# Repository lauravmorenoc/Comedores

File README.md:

# Comedores
Uno de los servicios que se busca mejorar por medio del proyecto "Campus Inteligente", corresponde al servicio de comedores de la Universidad Nacional de Colombia, sede Bogotá.

## Funcionamiento actual del sistema en la Universidad
Actualmente, los usuarios se dirigen a cualquiera de los comedores de la universidad, sin conocimiento previo de qué tan lleno se encuentra. Al llegar, hacen una fila física hasta el lugar en el que se sirven los almuerzos. Una vez aquí, toman una bandeja, y los empleados van presentando las opciones disponibles (por ejemplo, para escoger entre carne de res o pollo), de las cuales los usuarios eligen su opción favorita. En base a esta información, los empleados llenan los platos, que se van colocando en la bandeja. Al finalizar, se dirigen a la caja, en donde un operador les cobra una tarifa que depende si es estudiante sin beneficio alimentario, estudiante con este beneficio u otro tipo de usuario (visitante, docente, entre otros).

La siguiente imagen resume los aspectos anteriormente mencionados

## Primera solución presentada

## regulaciones respecto al uso del espectro electromagnético.

### Espectro electromagnético
Es la distribución energética del conjunto de las ondas electromagnéticas, yendo desde la longitud de onda más grande, a la longitud de onda más pequeña (o desde la frecuencia más baja, a la frecuencia más alta).

Uno de los usos principales del espectro son las telecomunicaciones, y por esta razón está regulado por el gobierno la radiación, distribución y recepción de las diferentes frecuencias. Las bandas varían dependiendo de la frecuencia/longitud de onda en varios grupos estándar:

Comparando los diferentes estándares se ven de la siguiente forma:

Respecto al espectro hay algunas regulaciones que es pertinente mencionar en relación al proyecto.

### Regulaciones
_Basado en el decreto 1078 de 2015 y la resolución 711 de 2016 de la ANE (Agencia Nacional del Espectro)_

#### Frecuencias para aplicaciones industriales, científicas y médicas (ICM)
Funcionamiento de equipos o de instalaciones destinados a producir y utilizar, en un espacio reducido, energía radioeléctrica con fines industriales, científicos y médicos, domésticos o similares, con exclusión de todas las aplicaciones de telecomunicación. Se muestran en la siguiente tabla:

Estas frecuencias pueden ser usadas para radiocomunicaciones de corto alcance (RCA), pero el usuario deben aceptar la potencial interferencia que se puede producir.

#### Frecuencias restringidas

Con el fin de evitar posibles interferencias a comunicaciones radioeléctricas sensibles tales como radionavegación aeronáutica, radioastronomía, operaciones de búsqueda y rescate y comunicaciones móviles, entre otras, los dispositivos de radiocomunicaciones de corto alcance y baja potencia (RCA) no podrán funcionar en las bandas descritas en la siguiente tabla:

#### Radiador intencional/radio aficionado
_Radiador intencional: Persona con interés en hacer algún tipo de transmisión usando el espectro._
_Radioaficionado: Persona con interés no comercial de hacer algún tipo de transmisión usando el espectro_

Para usar el espectro de forma comercial, la persona/entidad debe registrarse en el registro único del MINTIC, y ya que el uso será comercial, deben pagar contraprestaciones (impuestos) por el uso del espectro.

Los radioaficionados pueden usar el espectro sin pagar contraprestaciones. existen tres tipos de licencias para radioaficionados:

- Segunda o de Novicio
- Primera o de Experto
- Avanzada

#### Límites para radiadores intencionales o radio aficionados

A menos de estar incluido en alguna de las excepciones, las emisiones de cualquier radiador intencional no deberán superar los niveles de intensidad de campo que se especifican en la siguiente tabla:

A su vez estas son las restricciones de bandas y tipo de emisión:

#### Antenas

No se permite la operación de dispositivos con antenas diferentes a las suministradas o recomendadas por el fabricante, así mismo, no se pueden usar antenas que permitan que el sistema exceda los límites de potencia o campo eléctrico establecidos por regulación.

#### Referencias

https://www.suin-juriscol.gov.co/viewDocument.asp?id=30019521
https://normograma.mintic.gov.co/mintic/docs/pdf/resolucion_ane_0711_2016.pdf

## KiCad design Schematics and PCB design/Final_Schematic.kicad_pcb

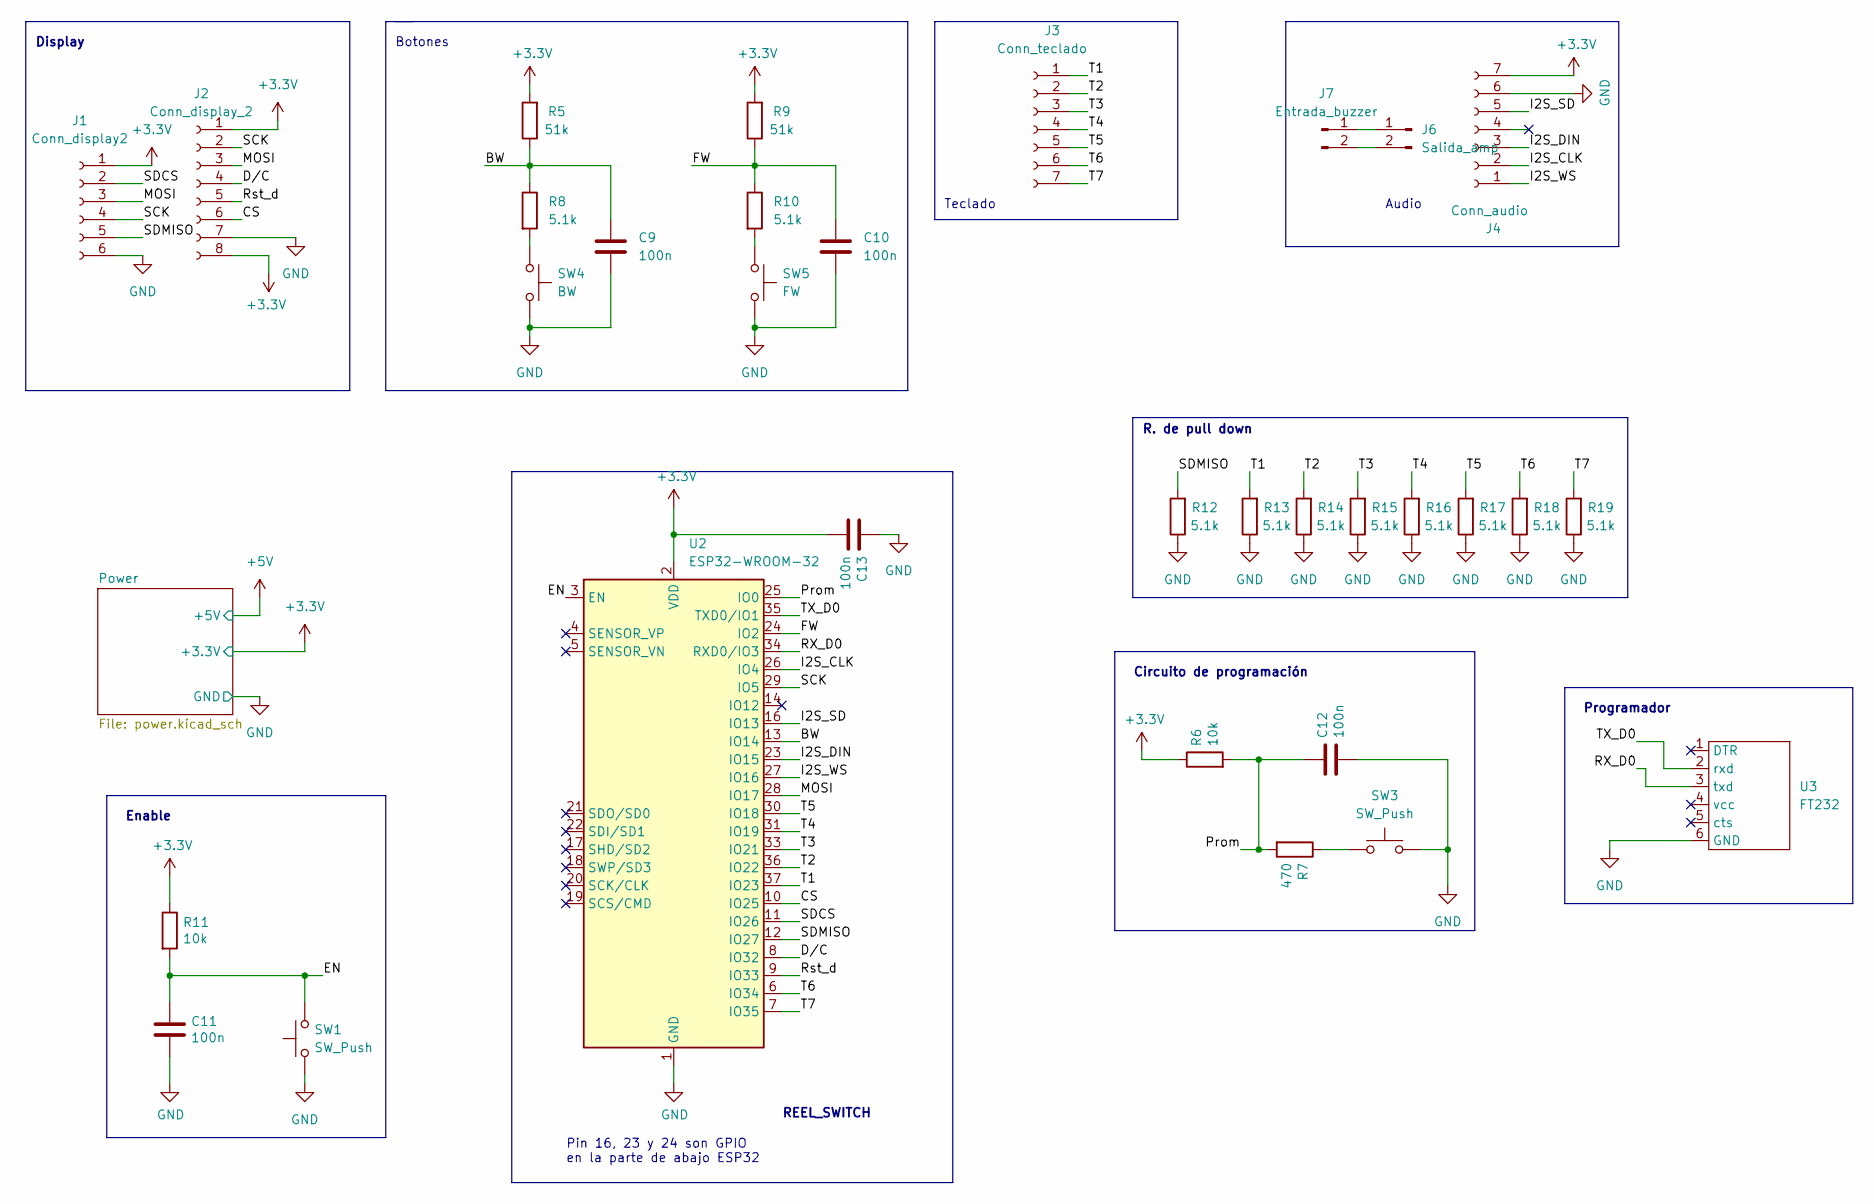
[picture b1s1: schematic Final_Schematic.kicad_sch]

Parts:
C9, C10, C11, C12, C13: 100n; C_0805_2012Metric_Pad1.18x1.45mm_HandSolder
J1: Conn_display2; PinHeader_1x06_P2.54mm_Vertical
J2: Conn_display_2; JST_EH_B8B-EH-A_1x08_P2.50mm_Vertical
J3: Conn_teclado; JST_EH_B7B-EH-A_1x07_P2.50mm_Vertical
J4: Conn_audio; PinSocket_1x07_P2.54mm_Vertical
J6: Salida_amp; PinSocket_1x02_P2.54mm_Vertical
J7: Entrada_buzzer; JST_EH_B2B-EH-A_1x02_P2.50mm_Vertical
R5, R9: 51k; R_0805_2012Metric_Pad1.20x1.40mm_HandSolder
R6, R11: 10k; R_0805_2012Metric_Pad1.20x1.40mm_HandSolder
R7: 470; R_0805_2012Metric_Pad1.20x1.40mm_HandSolder
R8, R10, R12, R13, R14, R15, R16, R17, R18, R19: 5.1k; R_0805_2012Metric_Pad1.20x1.40mm_HandSolder
SW1: SW_Push; SW_SPST_CK_RS282G05A3
SW3: SW_Push; SW_SPST_EVQQ2
SW4: BW; TerminalBlock_Altech_AK300-2_P5.00mm
SW5: FW; TerminalBlock_Altech_AK300-2_P5.00mm
U2: ESP32-WROOM-32
U3: FT232; PinSocket_1x06_P2.54mm_Vertical

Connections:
+3V3: C13.2, J1.1, J2.1, J2.8, J4.7, R5.2, R6.1, R9.2, R11.1, U2.2 (VDD); also elsewhere on the board
/BW: C9.2, R5.1, R8.1, U2.13 (IO14)
/CS: J2.6, U2.10 (IO25)
/D/C: J2.4, U2.8 (IO32)
/EN: C11.1, R11.2, SW1.2, U2.3 (EN)
/FW: C10.2, R9.1, R10.1, U2.24 (IO2)
/I2S_CLK: J4.2, U2.26 (IO4)
/I2S_DIN: J4.3, U2.23 (IO15)
/I2S_SD: J4.5, U2.16 (IO13)
/I2S_WS: J4.1, U2.27 (IO16)
/MOSI: J1.3, J2.3, U2.28 (IO17)
/Prom: C12.1, R6.2, R7.2, U2.25 (IO0)
/RX_D0: U2.34 (RXD0/IO3), U3.3 (txd)
/Rst_d: J2.5, U2.9 (IO33)
/SCK: J1.4, J2.2, U2.29 (IO5)
/SDCS: J1.2, U2.11 (IO26)
/SDMISO: J1.5, R12.2, U2.12 (IO27)
/T1: J3.1, R13.2, U2.37 (IO23)
/T2: J3.2, R14.2, U2.36 (IO22)
/T3: J3.3, R15.2, U2.33 (IO21)
/T4: J3.4, R16.2, U2.31 (IO19)
/T5: J3.5, R17.2, U2.30 (IO18)
/T6: J3.6, R18.2, U2.6 (IO34)
/T7: J3.7, R19.2, U2.7 (IO35)
/TX_D0: U2.35 (TXD0/IO1), U3.2 (rxd)
GND: C9.1, C10.1, C11.2, C12.2, C13.1, J1.6, J2.7, J4.6, R12.1, R13.1, R14.1, R15.1, R16.1, R17.1, R18.1, R19.1, SW1.1, SW3.2, SW4.2, SW5.2, U2.1 (GND), U2.15 (GND), U2.38 (GND), U2.39 (GND), U3.6 (GND); also elsewhere on the board
unnamed: J6.1, J7.1
unnamed: J6.2, J7.2
unnamed: R7.1, SW3.1
unnamed: R8.2, SW4.1
unnamed: R10.2, SW5.1

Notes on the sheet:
Circuito de programación
Botones
Pin 16, 23 y 24 son GPIO en la parte de abajo ESP32
R. de pull down
Display
Audio
Programador
Teclado
REEL_SWITCH
Enable

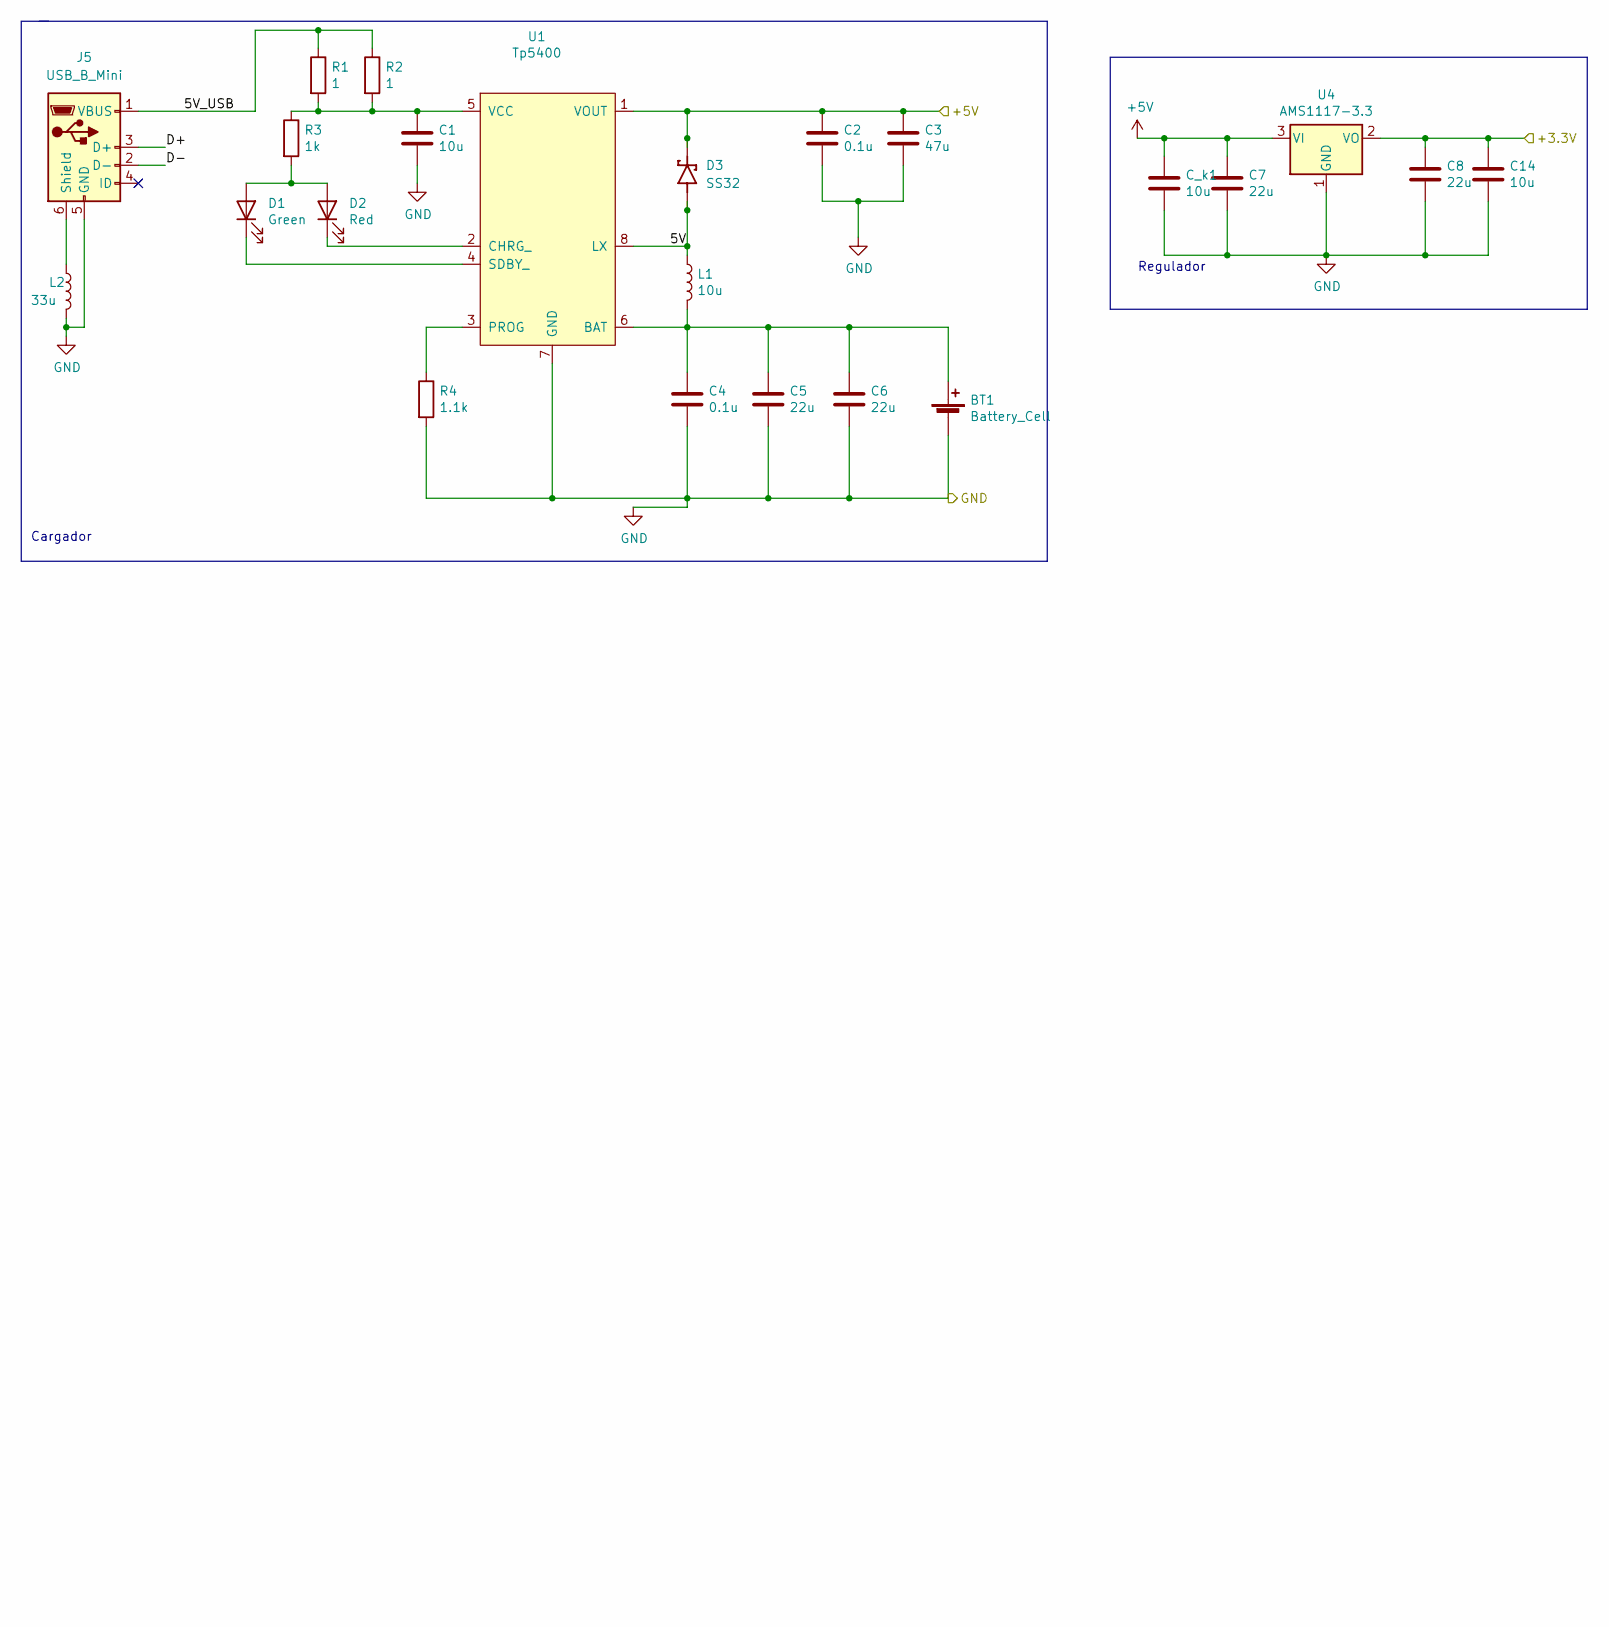
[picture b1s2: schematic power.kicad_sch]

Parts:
BT1: Battery_Cell; JST_PH_B2B-PH-K_1x02_P2.00mm_Vertical
C1, C14: 10u
C2, C4: 0.1u
C3: 47u
C5, C6, C7, C8: 22u
C_k1: 10u
D1: Green; LED_0805_2012Metric_Pad1.15x1.40mm_HandSolder
D2: Red; LED_0805_2012Metric_Pad1.15x1.40mm_HandSolder
D3: SS32; PARTREV Q2102
J5: USB_B_Mini; USB_Mini-B_AdamTech_MUSB-B5-S-VT-TSMT-1_SMD_Vertical
L1: 10u; L_6.3x6.3_H3
L2: 33u; L_6.3x6.3_H3
R1, R2: 1
R3: 1k
R4: 1.1k
U1: Tp5400; TP5410
U4: AMS1117-3.3; SOT-223-3_TabPin2

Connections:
+3V3: C8.1, C14.1, U4.2 (VO); also elsewhere on the board
+5V: C2.1, C3.1, C7.1, C_k1.1, D3.C, U1.1 (VOUT), U4.3 (VI)
/Power/5V: D3.A, L1.1, U1.8 (LX)
/Power/5V_USB: J5.1 (VBUS), R1.1, R2.1
/Power/D+: J5.3 (D+)
/Power/D-: J5.2 (D-)
GND: BT1.2 (-), C1.2, C2.2, C3.2, C4.2, C5.2, C6.2, C7.2, C8.2, C14.2, C_k1.2, J5.5 (GND), L2.2, R4.2, U1.7 (GND), U4.1 (GND); also elsewhere on the board
unnamed: BT1.1 (+), C4.1, C5.1, C6.1, L1.2, U1.6 (BAT)
unnamed: C1.1, R1.2, R2.2, R3.1, U1.5 (VCC)
unnamed: D1.1 (K), U1.4 (SDBY_)
unnamed: D1.2 (A), D2.2 (A), R3.2
unnamed: D2.1 (K), U1.2 (CHRG_)
unnamed: J5.6 (Shield), L2.1
unnamed: R4.1, U1.3 (PROG)

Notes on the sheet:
Regulador
Cargador

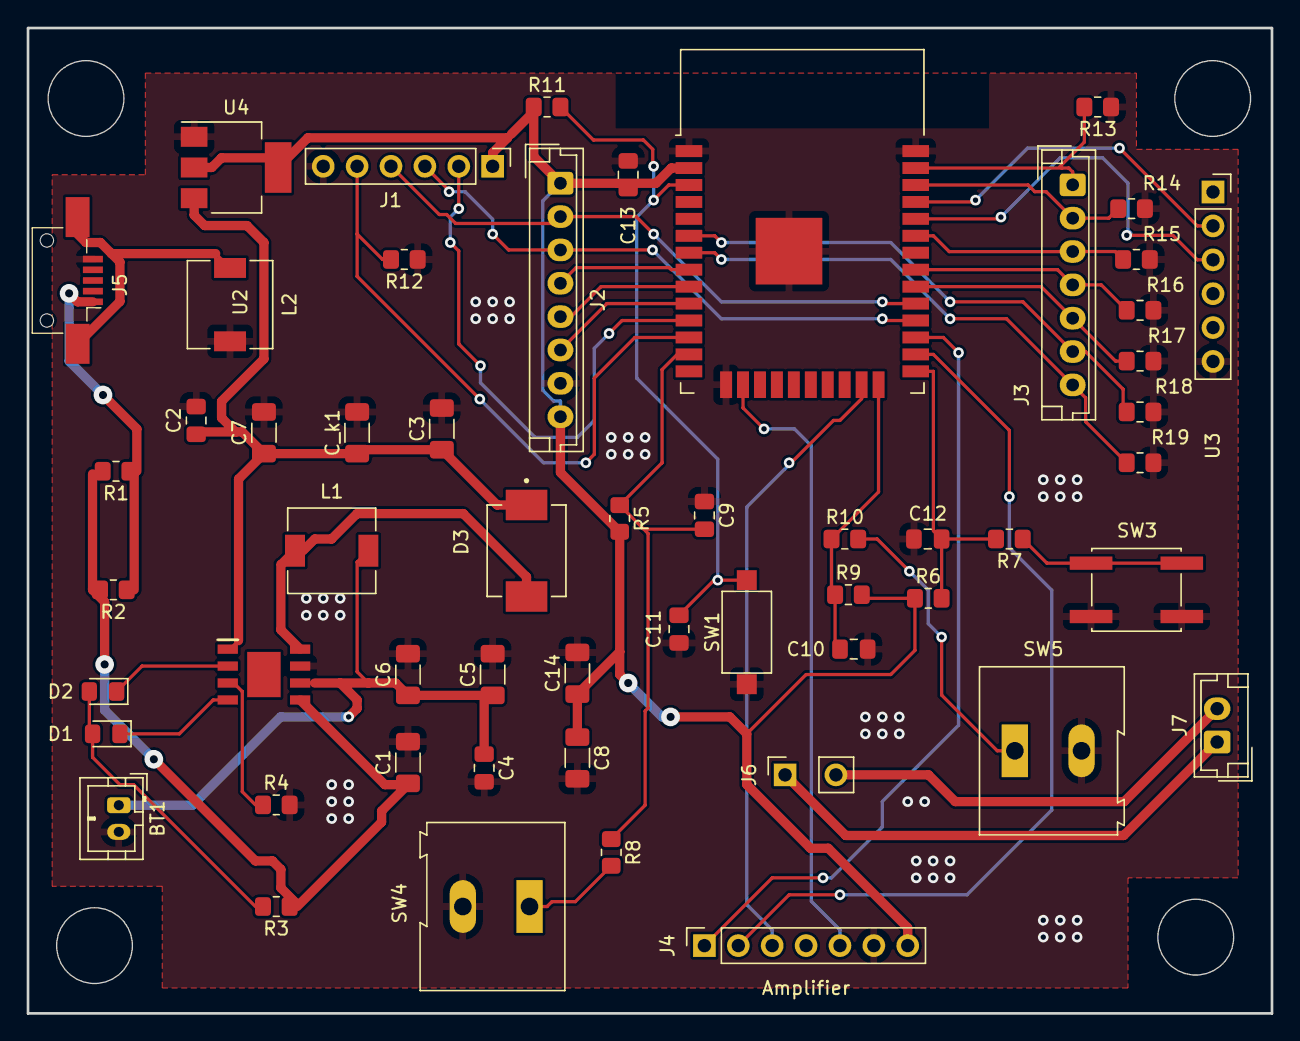
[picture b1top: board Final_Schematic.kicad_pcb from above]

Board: 2 copper layers, 93.2 x 73.9 mm, 55 parts (0 on the bottom side), 41 nets.

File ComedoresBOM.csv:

"Id";"Designator";"Package";"Quantity";"Designation";"Supplier and ref";
1;"C9,C11,C12,C13,C10";"C_0805_2012Metric_Pad1.18x1.45mm_HandSolder";5;"100n";;;
2;"C2,C4";"C_0603_1608Metric_Pad1.08x0.95mm_HandSolder";2;"0.1u";;;
3;"U4";"SOT-223-3_TabPin2";1;"AMS1117-3.3";;;
4;"R11,R6";"R_0805_2012Metric_Pad1.20x1.40mm_HandSolder";2;"10k";;;
5;"R9,R5";"R_0805_2012Metric_Pad1.20x1.40mm_HandSolder";2;"51k";;;
6;"FW";"TerminalBlock_Altech_AK300-2_P5.00mm";1;"FW";;;
7;"J4";"PinSocket_1x07_P2.54mm_Vertical";1;"Conn_audio";;;
8;"R7";"R_0805_2012Metric_Pad1.20x1.40mm_HandSolder";1;"470";;;
9;"SDCard";"PinHeader_1x06_P2.54mm_Vertical";1;"Conn_display2";;;
10;"J6";"PinSocket_1x02_P2.54mm_Vertical";1;"Salida_amp";;;
11;"D1";"LED_0805_2012Metric_Pad1.15x1.40mm_HandSolder";1;"Green";;;
12;"R12,R19,R8,R16,R15,R17,R18,R10,R13,R14";"R_0805_2012Metric_Pad1.20x1.40mm_HandSolder";10;"5.1k";;;
13;"R1,R2";"R_1218_3246Metric_Pad1.22x4.75mm_HandSolder";2;"1";;;
14;"R3";"R_1218_3246Metric_Pad1.22x4.75mm_HandSolder";1;"1k";;;
15;"D2";"LED_0805_2012Metric_Pad1.15x1.40mm_HandSolder";1;"Red";;;
16;"BW";"TerminalBlock_Altech_AK300-2_P5.00mm";1;"BW";;;
17;"C8,C5,C6,C7";"C_1210_3225Metric_Pad1.33x2.70mm_HandSolder";4;"22u";;;
18;"Display";"JST_EH_B8B-EH-A_1x08_P2.50mm_Vertical";1;"Conn_display_2";;;
19;"Keyboard";"JST_EH_B7B-EH-A_1x07_P2.50mm_Vertical";1;"Conn_teclado";;;
20;"Boot";"SW_SPST_EVQQ2";1;"SW_Push";;;
21;"U2";"ESP32-WROOM-32";1;"ESP32-WROOM-32";;;
22;"L1";"L_6.3x6.3_H3";1;"10u";;;
23;"C14,C1,C_k1";"C_1210_3225Metric_Pad1.33x2.70mm_HandSolder";3;"10u";;;
24;"Programmer";"PinSocket_1x06_P2.54mm_Vertical";1;"FT232";;;
25;"U1";"TP5410";1;"Tp5400";;;
26;"Buzzer";"JST_EH_B2B-EH-A_1x02_P2.50mm_Vertical";1;"Entrada_buzzer";;;
27;"MicroUSB";"USB_Mini-B_AdamTech_MUSB-B5-S-VT-TSMT-1_SMD_Vertical";1;"USB_B_Mini";;;
28;"D3";"SS32";1;"SS32";;;
29;"R4";"R_1218_3246Metric_Pad1.22x4.75mm_HandSolder";1;"1.1k";;;
30;"Battery";"JST_PH_B2B-PH-K_1x02_P2.00mm_Vertical";1;"Battery_Cell";;;
31;"L2";"L_6.3x6.3_H3";1;"33u";;;
32;"Enable";"SW_SPST_CK_RS282G05A3";1;"SW_Push";;;
33;"C3";"C_1210_3225Metric_Pad1.33x2.70mm_HandSolder";1;"47u";;;

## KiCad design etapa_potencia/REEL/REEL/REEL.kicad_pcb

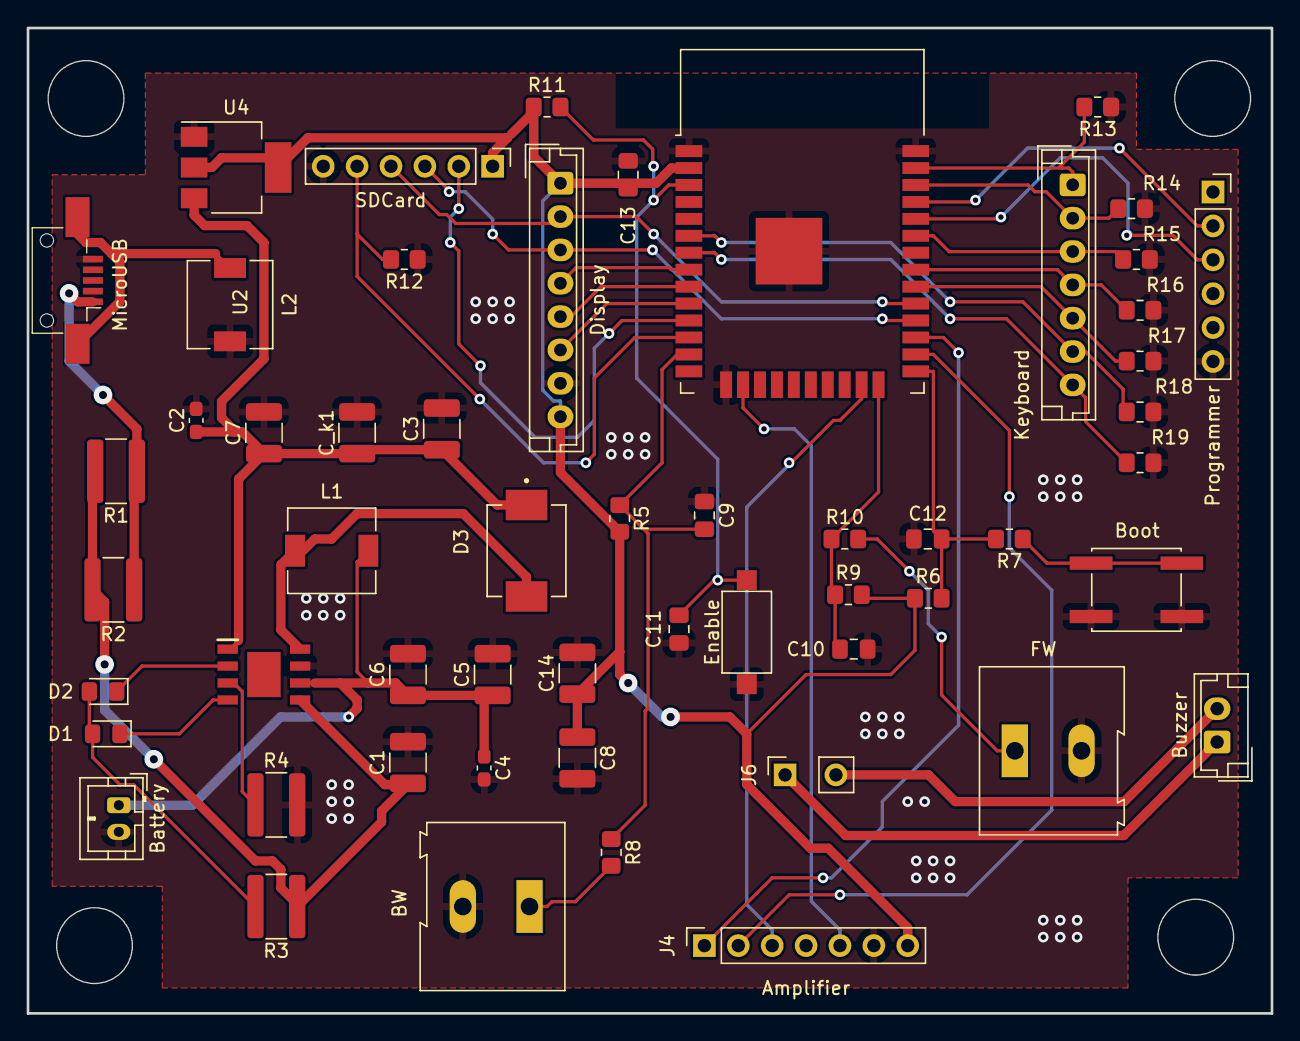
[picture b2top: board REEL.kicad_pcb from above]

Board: 2 copper layers, 93.2 x 73.9 mm, 55 parts (0 on the bottom side), 41 nets.

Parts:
BW: BW; TerminalBlock_Altech_AK300-2_P5.00mm
Battery: Battery_Cell; JST_PH_B2B-PH-K_1x02_P2.00mm_Vertical
Boot: SW_Push; SW_SPST_EVQQ2
Buzzer: Entrada_buzzer; JST_EH_B2B-EH-A_1x02_P2.50mm_Vertical
C1, C14: 10u; C_1210_3225Metric_Pad1.33x2.70mm_HandSolder
C2, C4: 0.1u; C_0603_1608Metric_Pad1.08x0.95mm_HandSolder
C3: 47u; C_1210_3225Metric_Pad1.33x2.70mm_HandSolder
C5, C6, C7, C8: 22u; C_1210_3225Metric_Pad1.33x2.70mm_HandSolder
C9, C10, C11, C12, C13: 100n; C_0805_2012Metric_Pad1.18x1.45mm_HandSolder
C_k1: 10u; C_1210_3225Metric_Pad1.33x2.70mm_HandSolder
D1: Green; LED_0805_2012Metric_Pad1.15x1.40mm_HandSolder
D2: Red; LED_0805_2012Metric_Pad1.15x1.40mm_HandSolder
D3: SS32
Display: Conn_display_2; JST_EH_B8B-EH-A_1x08_P2.50mm_Vertical
Enable: SW_Push; SW_SPST_CK_RS282G05A3
FW: FW; TerminalBlock_Altech_AK300-2_P5.00mm
J4: Conn_audio; PinSocket_1x07_P2.54mm_Vertical
J6: Salida_amp; PinSocket_1x02_P2.54mm_Vertical
Keyboard: Conn_teclado; JST_EH_B7B-EH-A_1x07_P2.50mm_Vertical
L1: 10u; L_6.3x6.3_H3
L2: 33u; L_6.3x6.3_H3
MicroUSB: USB_B_Mini; USB_Mini-B_AdamTech_MUSB-B5-S-VT-TSMT-1_SMD_Vertical
Programmer: FT232; PinSocket_1x06_P2.54mm_Vertical
R1, R2: 1; R_1218_3246Metric_Pad1.22x4.75mm_HandSolder
R3: 1k; R_1218_3246Metric_Pad1.22x4.75mm_HandSolder
R4: 1.1k; R_1218_3246Metric_Pad1.22x4.75mm_HandSolder
R5, R9: 51k; R_0805_2012Metric_Pad1.20x1.40mm_HandSolder
R6, R11: 10k; R_0805_2012Metric_Pad1.20x1.40mm_HandSolder
R7: 470; R_0805_2012Metric_Pad1.20x1.40mm_HandSolder
R8, R10, R12, R13, R14, R15, R16, R17, R18, R19: 5.1k; R_0805_2012Metric_Pad1.20x1.40mm_HandSolder
SDCard: Conn_display2; PinHeader_1x06_P2.54mm_Vertical
U1: Tp5400; TP5410
U2: ESP32-WROOM-32
U4: AMS1117-3.3; SOT-223-3_TabPin2

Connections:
+3V3: C8.1, C13.2, C14.1, Display.1, Display.8, J4.7, R5.2, R6.1, R9.2, R11.1, SDCard.1, U2.2 (VDD), U4.2 (VO)
+5V: C2.1, C3.1, C7.1, C_k1.1, D3.C, U1.1 (VOUT), U4.3 (VI)
/BW: C9.2, R5.1, R8.1, U2.13 (IO14)
/CS: Display.6, U2.10 (IO25)
/D/C: Display.4, U2.8 (IO32)
/EN: C11.1, Enable.2, R11.2, U2.3 (EN)
/FW: C10.2, R9.1, R10.1, U2.24 (IO2)
/I2S_CLK: J4.2, U2.26 (IO4)
/I2S_DIN: J4.3, U2.23 (IO15)
/I2S_SD: J4.5, U2.16 (IO13)
/I2S_WS: J4.1, U2.27 (IO16)
/MOSI: Display.3, SDCard.3, U2.28 (IO17)
/Power/5V: D3.A, L1.1, U1.8 (LX)
/Power/5V_USB: MicroUSB.1 (VBUS), R1.1, R2.1
/Prom: C12.1, R6.2, R7.2, U2.25 (IO0)
/RX_D0: Programmer.3 (txd), U2.34 (RXD0/IO3)
/Rst_d: Display.5, U2.9 (IO33)
/SCK: Display.2, SDCard.4, U2.29 (IO5)
/SDCS: SDCard.2, U2.11 (IO26)
/SDMISO: R12.2, SDCard.5, U2.12 (IO27)
/T1: Keyboard.1, R13.2, U2.37 (IO23)
/T2: Keyboard.2, R14.2, U2.36 (IO22)
/T3: Keyboard.3, R15.2, U2.33 (IO21)
/T4: Keyboard.4, R16.2, U2.31 (IO19)
/T5: Keyboard.5, R17.2, U2.30 (IO18)
/T6: Keyboard.6, R18.2, U2.6 (IO34)
/T7: Keyboard.7, R19.2, U2.7 (IO35)
/TX_D0: Programmer.2 (rxd), U2.35 (TXD0/IO1)
GND: BW.2, Battery.2 (-), Boot.2, C1.2, C2.2, C3.2, C4.2, C5.2, C6.2, C7.2, C8.2, C9.1, C10.1, C11.2, C12.2, C13.1, C14.2, C_k1.2, Display.7, Enable.1, FW.2, J4.6, L2.2, MicroUSB.5 (GND), Programmer.6 (GND), R4.2, R12.1, R13.1, R14.1, R15.1, R16.1, R17.1, R18.1, R19.1, SDCard.6, U1.7 (GND), U2.1 (GND), U2.15 (GND), U2.38 (GND), U2.39 (GND), U4.1 (GND)
unnamed: Battery.1 (+), C4.1, C5.1, C6.1, L1.2, U1.6 (BAT)
unnamed: C1.1, R1.2, R2.2, R3.1, U1.5 (VCC)
unnamed: D1.1 (K), U1.4 (SDBY_)
unnamed: D1.2 (A), D2.2 (A), R3.2
unnamed: D2.1 (K), U1.2 (CHRG_)
unnamed: L2.1, MicroUSB.6 (Shield)
unnamed: Buzzer.1, J6.1
unnamed: Buzzer.2, J6.2
unnamed: R4.1, U1.3 (PROG)
unnamed: Boot.1, R7.1
unnamed: BW.1, R8.2
unnamed: FW.1, R10.2

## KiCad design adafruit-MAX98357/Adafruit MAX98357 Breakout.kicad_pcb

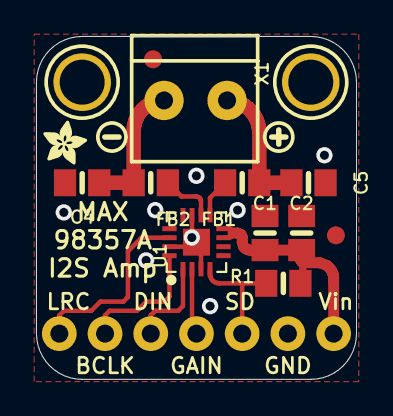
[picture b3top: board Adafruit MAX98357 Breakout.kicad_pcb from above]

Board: 2 copper layers, 17.8 x 19.0 mm, 18 parts (1 on the bottom side), 11 nets.

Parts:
C1: 0.1uF; 0805-NO
C2: 10uF; 0805-NO
C4, C5: 220pF; 0805-NO
FB1, FB2: Ferrite; 0805-NO
FID1, FID2: FIDUCIAL""; FIDUCIAL_1MM
JP1: 1X07_ROUND_76
R1: 1M; 0805-NO
U1: MAX98357A; QFN16_3MM
U$6: SYMBOL_PLUS
U$9, U$10: MOUNTINGHOLE2.5; MOUNTINGHOLE_2.5_PLATED
U$11: SYMBOL_MINUS
U$14: ADAFRUIT_2.5MM
U$15: PCBFEAT-REV-040
X1: TERMBLOCK_1X2-3.5MM

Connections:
BCLK: JP1.6, U1.16
DIN: JP1.5, U1.1
GAIN: JP1.4, U1.2
GND: C1.2, C2.2, C4.2, C5.2, JP1.2, U1.3, U1.11, U1.15, U1.THERMAL
LRCLK: JP1.7, U1.14
unnamed: FB2.1, U1.10
unnamed: FB1.1, U1.9
SD_MODE: JP1.3, R1.1, U1.4
VDD: C1.1, C2.1, JP1.1, R1.2, U1.7, U1.8
VO+: C5.1, FB1.2, X1.2
VO-: C4.1, FB2.2, X1.1

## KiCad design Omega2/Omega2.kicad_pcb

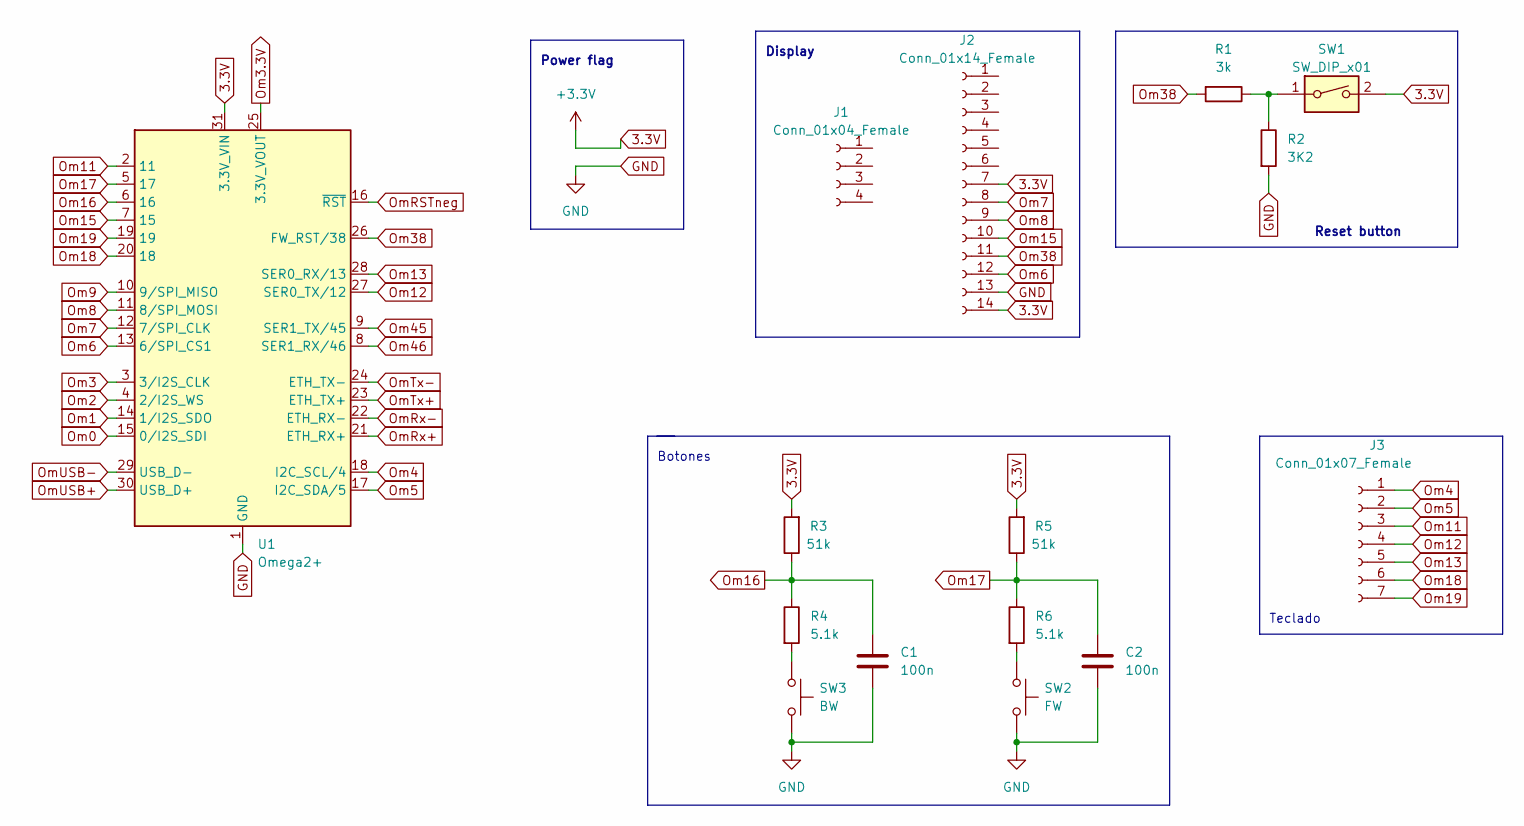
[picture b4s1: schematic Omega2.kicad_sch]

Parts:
C1, C2: 100n; C_0805_2012Metric_Pad1.18x1.45mm_HandSolder
J1: Conn_01x04_Female; PinSocket_1x04_P2.54mm_Vertical
J2: Conn_01x14_Female; PinSocket_1x14_P2.54mm_Vertical
J3: Conn_01x07_Female; PinSocket_1x07_P2.54mm_Vertical
R1: 3k; R_Axial_DIN0204_L3.6mm_D1.6mm_P7.62mm_Horizontal
R2: 3K2; R_Axial_DIN0204_L3.6mm_D1.6mm_P7.62mm_Horizontal
R3, R5: 51k; R_0805_2012Metric_Pad1.20x1.40mm_HandSolder
R4, R6: 5.1k; R_0805_2012Metric_Pad1.20x1.40mm_HandSolder
SW1: SW_DIP_x01; SW_PUSH_6mm
SW2: FW; TerminalBlock_Altech_AK300-2_P5.00mm
SW3: BW; TerminalBlock_Altech_AK300-2_P5.00mm
U1: Omega2+; Onion_Omega2+

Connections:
3.3V: J2.7, J2.14, R3.2, R5.2, SW1.2, U1.31 (3.3V_VIN)
GND: C1.1, C2.1, J2.13, R2.2, SW2.2, SW3.2, U1.1 (GND), U1.32 (GND)
unnamed: R1.1, R2.1, SW1.1
unnamed: R4.2, SW3.1
unnamed: R6.2, SW2.1
Om0: U1.15 (0/I2S_SDI)
Om1: U1.14 (1/I2S_SDO)
Om2: U1.4 (2/I2S_WS)
Om3: U1.3 (3/I2S_CLK)
Om3.3V: U1.25 (3.3V_VOUT)
Om4: J3.1, U1.18 (I2C_SCL/4)
Om5: J3.2, U1.17 (I2C_SDA/5)
Om6: J2.12, U1.13 (6/SPI_CS1)
Om7: J2.8, U1.12 (7/SPI_CLK)
Om8: J2.9, U1.11 (8/SPI_MOSI)
Om9: U1.10 (9/SPI_MISO)
Om11: J3.3, U1.2 (11)
Om12: J3.4, U1.27 (SER0_TX/12)
Om13: J3.5, U1.28 (SER0_RX/13)
Om15: J2.10, U1.7 (15)
Om16: C1.2, R3.1, R4.1, U1.6 (16)
Om17: C2.2, R5.1, R6.1, U1.5 (17)
Om18: J3.6, U1.20 (18)
Om19: J3.7, U1.19
Om38: J2.11, R1.2, U1.26 (FW_RST/38)
Om45: U1.9 (SER1_TX/45)
Om46: U1.8 (SER1_RX/46)
OmRSTneg: U1.16 (~RST)
OmRx+: U1.21 (ETH_RX+)
OmRx-: U1.22 (ETH_RX-)
OmTx+: U1.23 (ETH_TX+)
OmTx-: U1.24 (ETH_TX-)
OmUSB+: U1.30 (USB_D+)
OmUSB-: U1.29 (USB_D-)

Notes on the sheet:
Power flag
Botones
Teclado
Display
Reset button

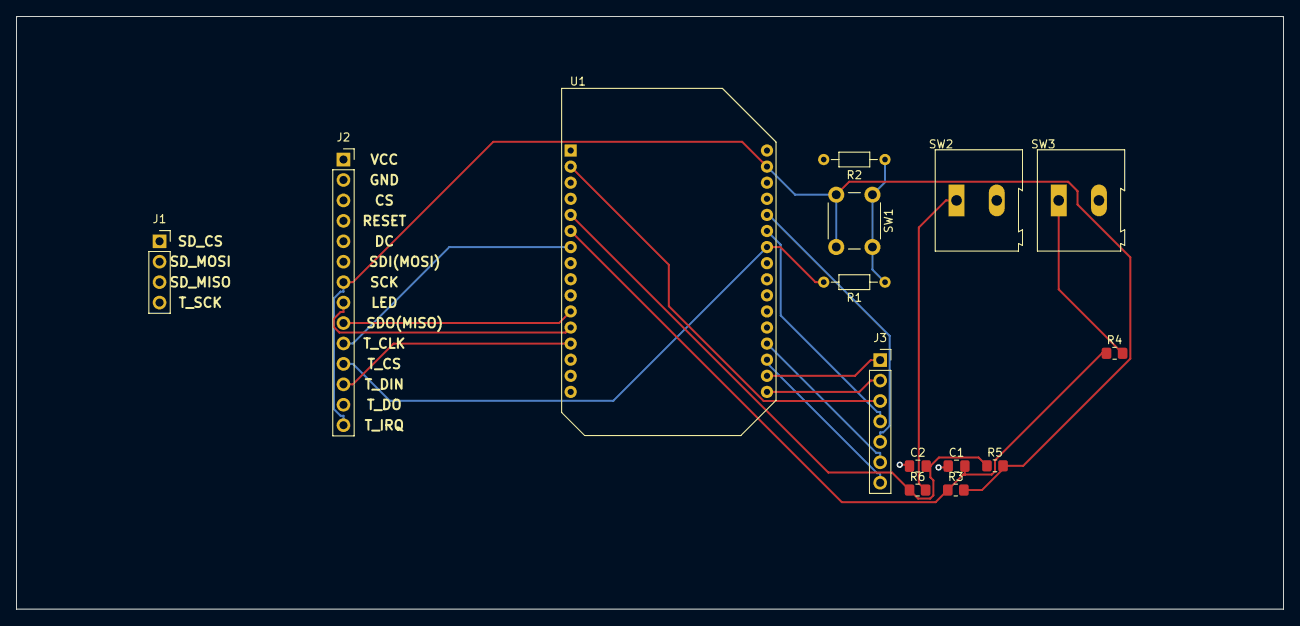
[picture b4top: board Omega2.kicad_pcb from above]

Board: 2 copper layers, 157.5 x 73.7 mm, 15 parts (0 on the bottom side), 19 nets.

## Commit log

2022-04-22 Esquemático en Kicad con interfaz y botón de reset
2022-04-25 Actualización de funcionamiento actual
2022-04-25 Update README.md
    Adición de normas ambientales
2022-04-25 Update README.md
    Agregación parcial info espectro electromagnético.
2022-04-25 Update README.md
    Cambio parcial espectro
2022-04-28 Organización display, botón de reset, power flag
2022-05-02 Adicion botones
2022-05-02 Adición Teclado
2022-05-06 edición pulsadores
2022-05-07 edicion
2022-05-07 edicion pcb
2022-05-07 Prueba de ruteo
2022-05-10 Adición módulo amplificación separado
2022-05-10 union de todo en el mismo esquemático
2022-05-10 prueba rama
2022-05-10 esquemático editado
2022-05-10 etapa_potencia
2022-05-10 Display
2022-05-12 Adición etapa de audio
2022-05-12 cambios etapa audio
2022-05-12 Edicion display y botones
2022-05-13 Conexiones corregidas, PCB ordenada
2022-05-13 adicion matriz vias
2022-05-15 Primera organización huellas
    Organización de huellas y conectores, falta parte de potencia
2022-05-16 Cambios en diagrama, separacion tierras, y capacitores
2022-05-17 modificaciones por caras
2022-05-17 etapa_audio
2022-05-17 Ubicación definida de los elementos
2022-05-17 Reorganización pcb
    Después de primera revisión del profe Camargo
2022-05-17 Ordenar huellas en PCB ahora sí
2022-05-17 PCB lista para rutear
2022-05-17 Cambio orden pines etapa de audio
2022-05-17 Primer ruteo PCB
2022-05-19 Adición conector de tarjeta SD
2022-05-19 Nombres en capa silkscreen
2022-05-19 Edicion pcb rutas
2022-05-20 Últimos arreglos PCB
    Resistencias de pull down de teclado y pin MISO de la sd, pin 12 queda libre, pines 34 y 35 quedan de entrada únicamente.
2022-05-20 Corrección errores DCR
2022-05-21 Archivos gerber, drill, BOM y pos
2022-05-25 Organización y adición de códigos Micropython
    Organización de carpetas, adición de código MQTT 1.0 y primera prueba con Display
2022-05-25 Organización carpetas again
2022-05-31 Commit de prueba
2022-05-31 Commit de prueba x2
2022-06-01 Corrección error MQTT
2022-06-10 Avance código MicroPython
2022-06-11 Adicion codigos micropython
2022-06-14 Función completa de display y logo UN
2022-06-15 ESP to PC MQTT connection tested
2022-06-17 MQTT module updated
    PC reads ID correctly and returns data dictionary. However, the ESP is publishing back what it is receiving from PC. Working on it.
2022-06-17 ESP MQTT echo problem solved in host module
    Host module modified, so when the ESP returns the echo message, the host doesn't react to it
2022-06-20 Communications receiving code ready
    Audio function muss be added
2022-06-20 Update display ticket from communications module tested
    Falta integrar funciones de teclado, botones y audio
2022-06-20 Small change in communications detecting incoming messages
2022-06-20 Same as last commit, forgot to update a file
2022-06-21 Minor changes
    Cambié el last_pending...=false para que fuera general en el main, agregué que mire si el comedor al actualizar el turno coincide, y que mire si la persona está registrada para imprimir el nombre o p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
2022-06-21 Adicion codigos Juan
2022-06-21 pre-keyboard function and SI broker added
2022-06-21 Buttons and audio union to main code
2022-06-21 More tests
2022-06-23 Código con comunicaciones, audio y botones probado
2022-06-23 play_tone
2022-06-30 Asegurarnos por si algo
2022-07-02 Integración código teclado
